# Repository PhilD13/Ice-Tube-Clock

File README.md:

Ice-Tube-Clock
==============

Ice Tube Clock - PhilD13

This is my working directory fork of the icetube clock from Adafruit that will incorporate various board changes and component updates as 
I learn more about Eagle Cad.

The working directory is where the latest working files are located. 

Transistor version of main board is a modified version of the Adafruit main board. Some components and traces have been moved around to 
accommodate the use of a 2N2907 transistor for Q3 and the R6 1K resistor that is required for the transistor. Of course, the transistor version can be used 
with a FET by replacing R6 with a jumper

Schematic and Part Changes
1.) Change the ATmega168V-10PU to a ATMEGA328P-PU-ND to provide memory space for the use of the  xmas-icetube firmware by John Archie.
		See: https://github.com/johngarchie/xmas-icetube/

2.) Change value of R3 from 22 ohm to 11 ohm. The 11 ohm resistor can also be changed to a jumper wire if desired to help correct dim digits.
		See: http://forums.adafruit.com/viewtopic.php?f=41&t=39298&p=203372&hilit=11+ohm#p203372
	and
		http://forums.adafruit.com/viewtopic.php?p=179107#p179107

3.) Change values of C8 and C9 from 20pf to 10pf for better timekeeping. 
		See: http://forums.adafruit.com/viewtopic.php?p=189366#p189366

4.) Change Q3/Q4 from ZVP3306A FET to a ZVP2110A (still P-channel) so mount matching board silk screen 
		See: http://forums.adafruit.com/viewtopic.php?f=41&t=39298&p=203372&hilit=ZVP2110#p203372

5.) Changed Q3 to a 2N2907 transistor/ 1K resistor combo in transistor version of board. Can use a jumper and FET if desired. Board will 
accommodate either one. 

Tips:
The Ice Cube Clock will blink the display after a power loss. This is normal and acts like most other commercial clocks to warn of a potential 
time loss due to a power loss. Toggle through the Menu options to stop the blinking.
- This how it's supposed to work anytime the clock senses a loss of power and is not an indication of the FET being installed backwards 
or some other problem. 

The FET Q3 is designed into the clock as a high side switch to disconnect the voltage from the tube filament (bias) and the voltage (VCC) 
from the MAX6921 VFD drive chip in the event of a loss of normal input voltage. This leaves only the ATMEGA328P-PU-ND processor powered by 
the battery and a good battery can power the processor for at least a couple weeks.

The Q3 FET will still work if it is installed backwards. The clock will still work and display time just fine. Due to how a FET is 
constructed, the FET will not fully turn off if it is reversed in the circuit and will still pass current which will cause the battery to quickly die

So, if the clock does not keep time while only on battery power then the FET Q3 is probably installed backwards causing it to not turn 
off properly when power is removed.

I have found that the current ZVP3306A (from Diodes Inc.) p-channel enhancement mode FET supplied for Q3 has the correct orientation when 
installed with the rounded side with writing on it facing the rounded side of the silkscreen outline on the board as in the photo below. 
This orientation also matches the schematic for the clock. 
This is contrary to the assembly instructions. http://learn.adafruit.com/ice-tube-clock-kit/board-assembly
See this thread for more information: http://www.adafruit.com/forums/viewtopic.php?f=41&t=43209

The clock when first built and powered on has the brightness defaulted (is set) to the dimmest setting making it very hard to see
to set in normal room brightness. Turn the room lights out.

On the Adafruit firmware, the Brightness setting is the 4th menu in. Press the Menu button 4 times, then press the + button 2 or 3 times to set brightness higher
before trying to set other options. This makes it much easier to read the clock while initially setting and getting used to the menus 
and can be adjusted later as desired.

When installing the buttons on the board, make sure to get all of the buttons flat to the circuit board and keep them flat while soldering 
them in place. If the buttons are not flat to the circuit board, their black stems won't fit properly through the case holes and may stick 
in when pressed, so pay close attention to that detail. If they do get soldered in not quite flat then you may need to make the button 
holes in the case back slightly larger. Use care, the proper size drill bit (one size larger than the hole is good) in a battery drill, 
go slow and drill from both sides of the hole or the plastic may break.

Identify the tube you have
	There are 22 holes in the Tubes PC board for tube wires.
	Count the wires on the tube. Some tubes have 19 wires and some tubes may have 22 wires (three are not connected inside of tube in that case). 
	
	If the tube has 19 wires, the wire spacing will be different and you'll see two wires that seem 'farther apart' than the others. 
	Begin by threading those two front wires into the PC board so that they straddle the 3 NC (not connected) pins. 
	
	If the tube has 22 wires, then the wire spacing will be even all around the tube and you will see three non-connected pins inside the glass tube.
		Thread the three non-connected wires, so they pass through the holes marked "Display NC" (not connected).
 
	For both tube types, pass the remaining wires through so they pass straight through and are not crossed or bent.
	Pass the wires into the holes only a little way and bend wire over. After all the wires are inserted in their proper holes, then begin working 
	the tube board down towards the base of the tube.
 
Allow plenty of time to fit the tube to the circuit board it mounts on and be patient. 
	Tweezers and a small pair of needle nose pliers can help straighten any wires and assist in getting them through the holes. 
	Don't try to force any wires through their holes. 
	Inserting each wire a little ways into its corresponding hole, then bending the wires end over so it will stay in the hole
	makes it easier to maneuver the tube and board while inserting wires.
	Once all the wires are in their proper holes, begin moving the PC board up the wires toward the tube end. Use fingers, tweezers, 
	and needle nose pliers as necessary to assist in sliding the PC board into proper position.

Check the fit of the tube in the case before soldering. 
	Do this by mounting the case base plate (with the setting instructions) to 
	the main PC board. Then assemble the back side and the left side case panels to the base plate and adjust the position as needed.
	A distance of about 4 - 6 mm between the glass tube end and the PC board front should be a good position. Check that the tubes 
	PC board sits flush in the female header when the tube is in the case.
	
Tack the tube in place
	Once the wiring of the tube to the PC board is verified to be correct, there are no crossed wires, no shorted wires, 
	and the tube distance is proper  Solder tack two upper and two lower wires to hold the tube in place on the PC board.
	Remove the tube from the case and header. Solder all the wires and trim very close to PC board so everything fits 
	properly when the case is assembled. 	

Data Sheet Links and ETC.
	ATMEGA328P-PU-ND DigiKey part: http://www.digikey.com/product-detail/en/ATMEGA328P-PU/ATMEGA328P-PU-ND/1914589
	ATMEGA328P-PU-ND Data sheet: http://www.atmel.com/Images/Atmel-8271-8-bit-AVR-Microcontroller-ATmega48A-48PA-88A-88PA-168A-168PA-328-328P_datasheet.pdf
	
	FET ZVP2110A DigiKey part: http://www.digikey.com/product-detail/en/ZVP2110A/ZVP2110A-ND/92620
	FET ZVP2110A Data Sheet: http://www.diodes.com/datasheets/ZVP2110A.pdf
	
	MAX6921AQI+-ND DigiKey part: http://www.digikey.com/product-detail/en/MAX6921AQI%2B/MAX6921AQI%2B-ND/1512036
	MAX6921AQI+-ND Data Sheet: http://datasheets.maximintegrated.com/en/ds/MAX6921-MAX6931.pdf
	
	IRFD110PBF-ND DigiKey part: http://www.digikey.com/product-detail/en/IRFD110PBF/IRFD110PBF-ND/812472
	IRFD110PBF-ND Data Sheet: http://www.vishay.com/doc?91127

Older parts for reference:	
	ATMEGA168V-10PU-ND DigiKey part: http://www.digikey.com/product-detail/en/ATMEGA168V-10PU/ATMEGA168V-10PU-ND/735447
	ATMEGA168V-10PU-ND http://www.atmel.com/Images/doc2545.pdf
	
	FET ZVP3306A DigiKey part: http://www.digikey.com/product-detail/en/ZVP3306A/ZVP3306A-ND/92625
	FET ZVP3306A Data Sheet: http://www.diodes.com/datasheets/ZVP3306A.pdf
	
	Original Ice Tube Clock board and schematic, firmware: https://github.com/adafruit/Ice-Tube-Clock

Firmware:	
	Really Good Firmware: https://github.com/johngarchie/xmas-icetube/

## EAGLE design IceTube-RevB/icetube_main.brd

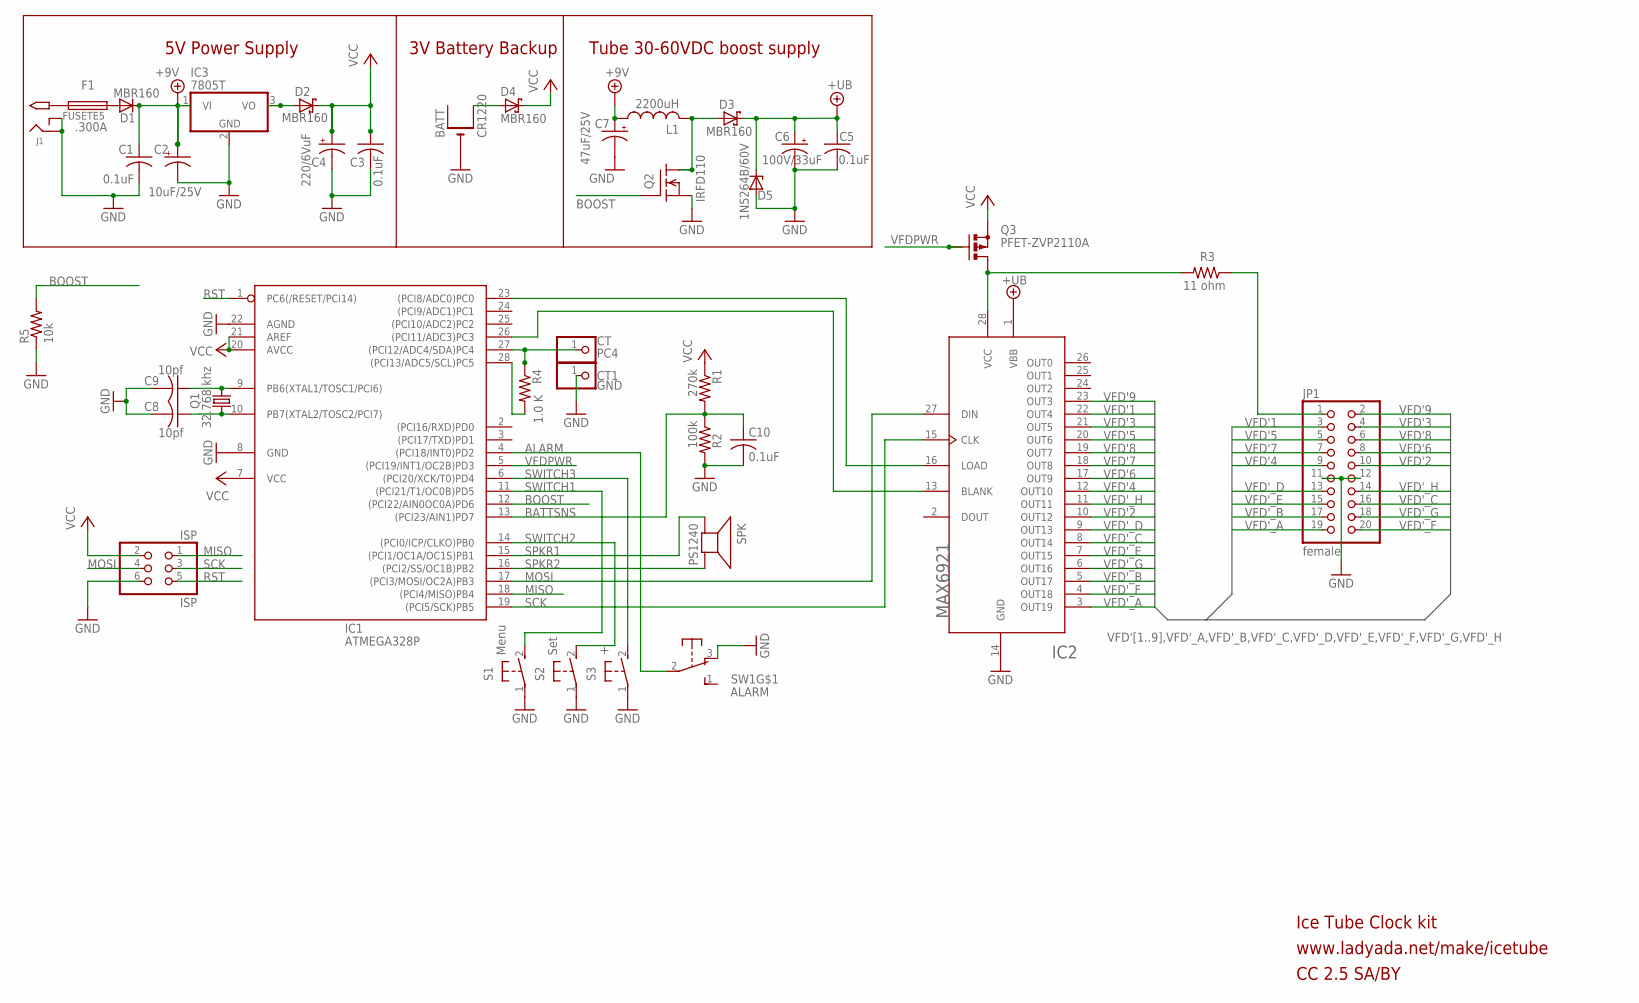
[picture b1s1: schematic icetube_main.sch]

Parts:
BATT: CR1220; CR1220-THM
C1, C3: 0.1uF; C025-025X050
C2: 10uF/25V; E2,5-6
C4: 220/6VuF; E2,5-6
C5, C10: 0.1uF; C025-024X044
C6: 100V/33uF; E3,5-8
C7: 47uF/25V; E2,5-6
C8, C9: 10pf; C025-025X050
CT: PC4; 1X01
CT1: GND; 1X01
D1, D2, D3, D4: MBR160; DO41-10
D5: 1N5264B/60V; DO41Z10
F1: FUSETE5; TE5
IC1: ATMEGA328P; DIL28/3
IC2: MAX6921; PLCC-S28
IC3: 7805T; TO220H
ISP: ISP; 2X03
J1: 2.1MMJACKTHM; PJ-102A
JP1: female; 2X10
L1: 2200uH; 6000
Q1: 32.768 khz; TC26V
Q2: IRFD110; DIL04
Q3: PFET-ZVP2110A; TO92-OVAL
R1: 270k; 0207/10
R2: 100k; 0207/10
R3: 11 ohm; 0207/10
R4: 1.0 K; 0207/5V
R5: 10k; 0207/5V
S1: Menu; B3F-31XX
S2: Set; B3F-31XX
S3: +; B3F-31XX
SPK: PS1240; PS12
SW1: ALARM; OS102011MA1Q

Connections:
+9V: C1.1, C2.+, C7.+, D1.C, IC3.1 (VI), L1.1
+UB: C5.1, C6.+, D3.C, D5.C, IC2.1 (VBB)
ALARM: IC1.4 ((PCI18/INT0)PD2), SW1.2
BATTSNS: C10.1, IC1.13 ((PCI23/AIN1)PD7), R1.2, R2.1
BLANK: IC1.26 ((PCI11/ADC3)PC3), IC2.13 (BLANK)
BOOST: IC1.12 ((PCI22/AIN0OC0A)PD6), Q2.3 (G), R5.2
GND: BATT.-, C1.2, C2.-, C3.2, C4.-, C5.2, C6.-, C7.-, C8.2, C9.2, C10.2, CT1.1, D5.A, IC1.8 (GND), IC1.22 (AGND), IC2.14 (GND), IC3.2 (GND), ISP.6, J1.RING, J1.RING_SW, JP1.11, JP1.12, Q2.4 (S), R2.2, R5.1, S1.1, S2.1, S3.1, SW1.3 (O)
LOAD: IC1.23 ((PCI8/ADC0)PC0), IC2.16 (LOAD)
MISO: IC1.18 ((PCI4/MISO)PB4), ISP.1
MOSI: IC1.17 ((PCI3/MOSI/OC2A)PB3), IC2.27 (DIN), ISP.4
unnamed: C9.1, IC1.9 (PB6(XTAL1/TOSC1/PCI6)), Q1.2
unnamed: D3.A, L1.2, Q2.1 (D), Q2.2 (D1)
unnamed: C8.1, IC1.10 (PB7(XTAL2/TOSC2/PCI7)), Q1.1
unnamed: F1.1, J1.TIP
unnamed: D1.A, F1.2
unnamed: BATT.+2 (+1), D4.A
unnamed: IC1.28 ((PCI13/ADC5/SCL)PC5), R4.2
unnamed: JP1.1, R3.1
unnamed: IC2.28 (VCC), Q3.3 (D), R3.2
unnamed: CT.1, IC1.27 ((PCI12/ADC4/SDA)PC4), R4.1
unnamed: D2.A, IC3.3 (VO)
RST: IC1.1 (PC6(/RESET/PCI14)), ISP.5
SCK: IC1.19 ((PCI5/SCK)PB5), IC2.15 (CLK), ISP.3
SPKR1: IC1.15 ((PCI1/OC1A/OC1S)PB1), SPK.P$1 (+)
SPKR2: IC1.16 ((PCI2/SS/OC1B)PB2), SPK.P$2 (-)
SWITCH1: IC1.11 ((PCI21/T1/OC0B)PD5), S1.2 (S)
SWITCH2: IC1.14 ((PCI0/ICP/CLKO)PB0), S2.2 (S)
SWITCH3: IC1.6 ((PCI20/XCK/T0)PD4), S3.2 (S)
VCC: C3.1, C4.+, D2.C, D4.C, IC1.7 (VCC), IC1.20 (AVCC), IC1.21 (AREF), ISP.2, Q3.1 (S), R1.1
VFD'1: IC2.22 (OUT4), JP1.3
VFD'2: IC2.10 (OUT12), JP1.10
VFD'3: IC2.21 (OUT5), JP1.4
VFD'4: IC2.12 (OUT10), JP1.9
VFD'5: IC2.20 (OUT6), JP1.5
VFD'6: IC2.17 (OUT9), JP1.8
VFD'7: IC2.18 (OUT8), JP1.7
VFD'8: IC2.19 (OUT7), JP1.6
VFD'9: IC2.23 (OUT3), JP1.2
VFD'_A: IC2.3 (OUT19), JP1.19
VFD'_B: IC2.5 (OUT17), JP1.17
VFD'_C: IC2.8 (OUT14), JP1.16
VFD'_D: IC2.9 (OUT13), JP1.13
VFD'_E: IC2.7 (OUT15), JP1.15
VFD'_F: IC2.4 (OUT18), JP1.20
VFD'_G: IC2.6 (OUT16), JP1.18
VFD'_H: IC2.11 (OUT11), JP1.14
VFDPWR: IC1.5 ((PCI19/INT1/OC2B)PD3), Q3.2 (G)

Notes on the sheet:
5V Power Supply
3V Battery Backup
Tube 30-60VDC boost supply
Ice Tube Clock kit
www.ladyada.net/make/icetube
CC 2.5 SA/BY

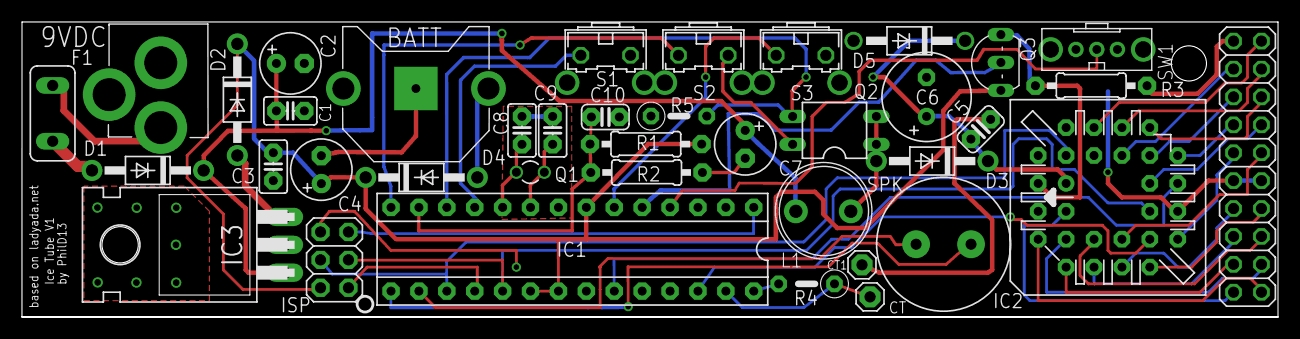
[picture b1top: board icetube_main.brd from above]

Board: 2 copper layers, 114.3 x 26.9 mm, 39 parts (0 on the bottom side), 47 nets.

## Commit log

2013-08-27 working branch commit
2013-08-27 Added OSH_Parks Eagle Cad DRU file
2013-08-27 Add xmas-icetube-firmware
2013-08-27 cleanup of directory
2013-08-27 Board and schematic as uploaded to OSH Park, by their upload board feature.
2014-02-19 add transistor version
2014-02-19 cleanup
2014-02-19 removed unnecessary files
2014-02-19 add BOM and restructure
2014-02-19 corrected BOM entry
2014-10-25 Added branch RevB
